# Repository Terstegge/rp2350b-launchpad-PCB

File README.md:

# RP2350 Launchpad

This repository contains the KiCad design files for a TI-style Launchpad
board with the RP2350B microcontroller. The board has the following
features:

- RP2350 microcontroller with 48 GPIOs (8 of these can be used as ADC inputs)
- 8MB of flash and 8MB of PSRAM
- A single red LED (connected to GPIO 38). Can be disabled with a jumper.
- Eight WS2812 RGB LEDs (connected to GPIO 39)
- A reset button
- Two user buttons (S1/S2 connected to GPIO 28/29)
- USB-C socket connected to the target RP2350
- A small button to let the RP2350 start in mass-storage mode for programming.
  This is usually not needed when using the debugger.
- A target isolation jumper block which can be used to completely disconnect
  the targer from power supply and debugging signals.
- A RP2040-based picoprobe debug probe which also forwards UART traffic from
  the target to the connected PC. Three LEDs signal UART RX/TX activity
  and SWD activity.
- Additional header for unused GPIOs of the picoprobe RP2040, which could
  be used for logic analyzer inputs or other purposes.
- Flexible power supply by either using
  * the upper USB-C socket connected to the debugger
  * a connected 3,7V LiPo battery
  * the lower USB-C socket connected to the target

  These three options are selectble with a small switch
- Integrated LiPo charger. The battery will be charged when the board is
  powered from the upper USB-C socket. Charging is signalled with a LED.
  The battery voltage can be read by the RP2350 using ADC channel 7.
- In all power scenarios, 3.3V and 5V are available. When using the
  battery as the power source, the 5V supply is generated with a step-up
  converter.

Why was this board designed? I have been using the MSP432 Launchpad from TI for
quite a while in university classes teaching microcontroller technology.
Unfortunately TI has stopped producing all MSP432-related products. Still we
have lots of TI boosterpack-boards like the Educational Boosterpack MK II.
To be able to use these Boosterpacks also in the future, a new Launchpad had
to be found or designed. The RP2350B is a very interesting microcontroller,
and, what is quite important for educational purposes, it has excellent
documentation. So this board came to life. As far as I know this is the only
RP2350 board including a picoprobe debugger, which makes programming for the
students a lot easier.

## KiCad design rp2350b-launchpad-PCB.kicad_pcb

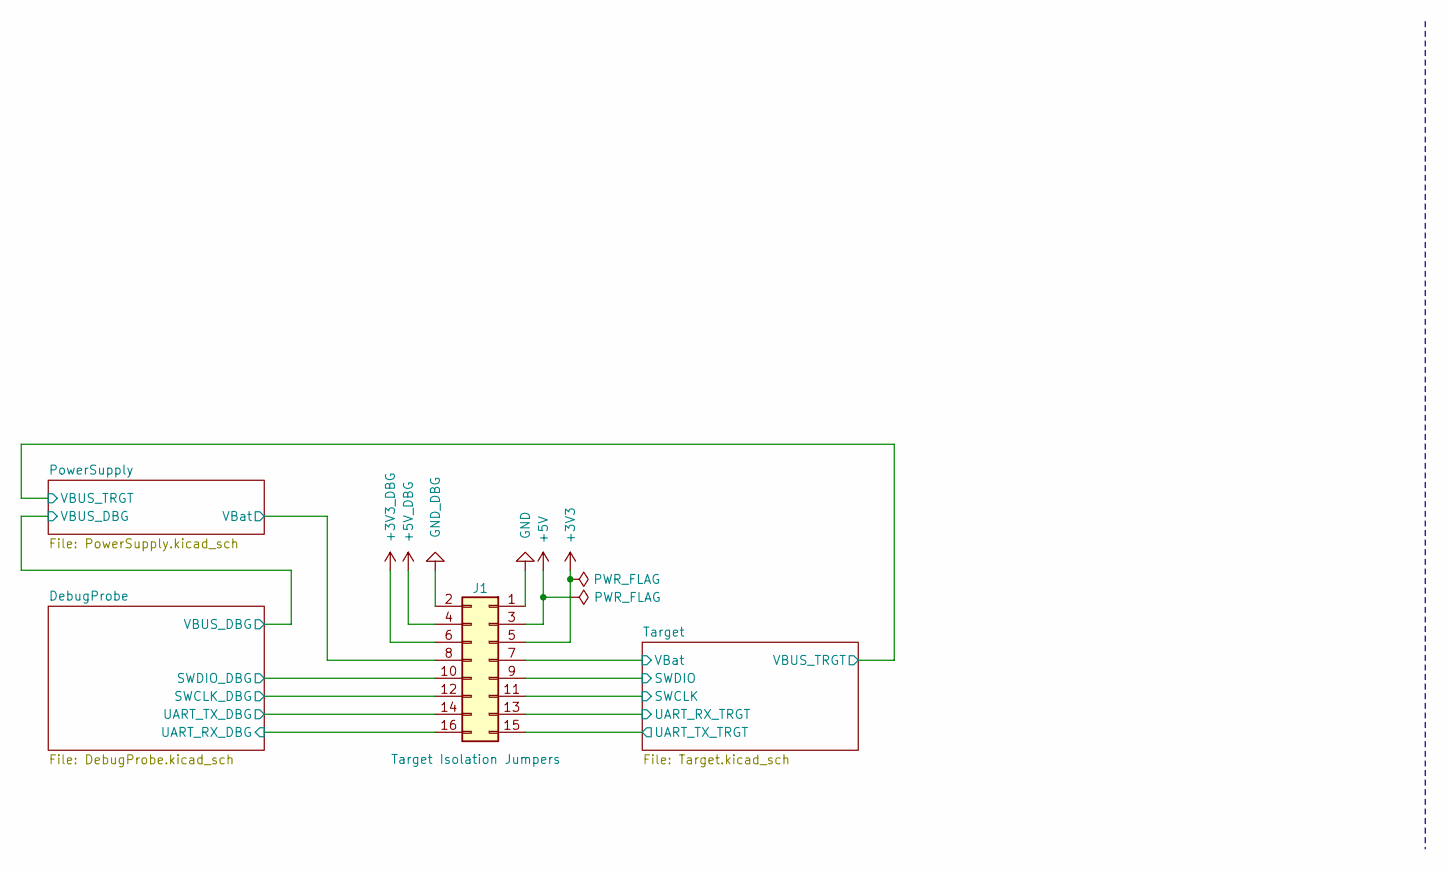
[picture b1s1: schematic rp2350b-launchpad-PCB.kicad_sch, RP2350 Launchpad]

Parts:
J1: Target Isolation Jumpers; PinHeader_2x08_P2.54mm_Vertical

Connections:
+3V3: J1.5; also elsewhere on the board
+3V3_DBG: J1.6; also elsewhere on the board
+5V: J1.3; also elsewhere on the board
+5V_DBG: J1.4; also elsewhere on the board
/DebugProbe/SWCLK_DBG: J1.12; also elsewhere on the board
/DebugProbe/SWDIO_DBG: J1.10; also elsewhere on the board
/DebugProbe/UART_RX_DBG: J1.16; also elsewhere on the board
/DebugProbe/UART_TX_DBG: J1.14; also elsewhere on the board
/PowerSupply/VBat: J1.8; also elsewhere on the board
/Target/ADC7: J1.7; also elsewhere on the board
/Target/SWCLK: J1.11; also elsewhere on the board
/Target/SWDIO: J1.9; also elsewhere on the board
/Target/UART_RX_TRGT: J1.13; also elsewhere on the board
/Target/UART_TX_TRGT: J1.15; also elsewhere on the board
GND: J1.1; also elsewhere on the board
GND_DBG: J1.2; also elsewhere on the board

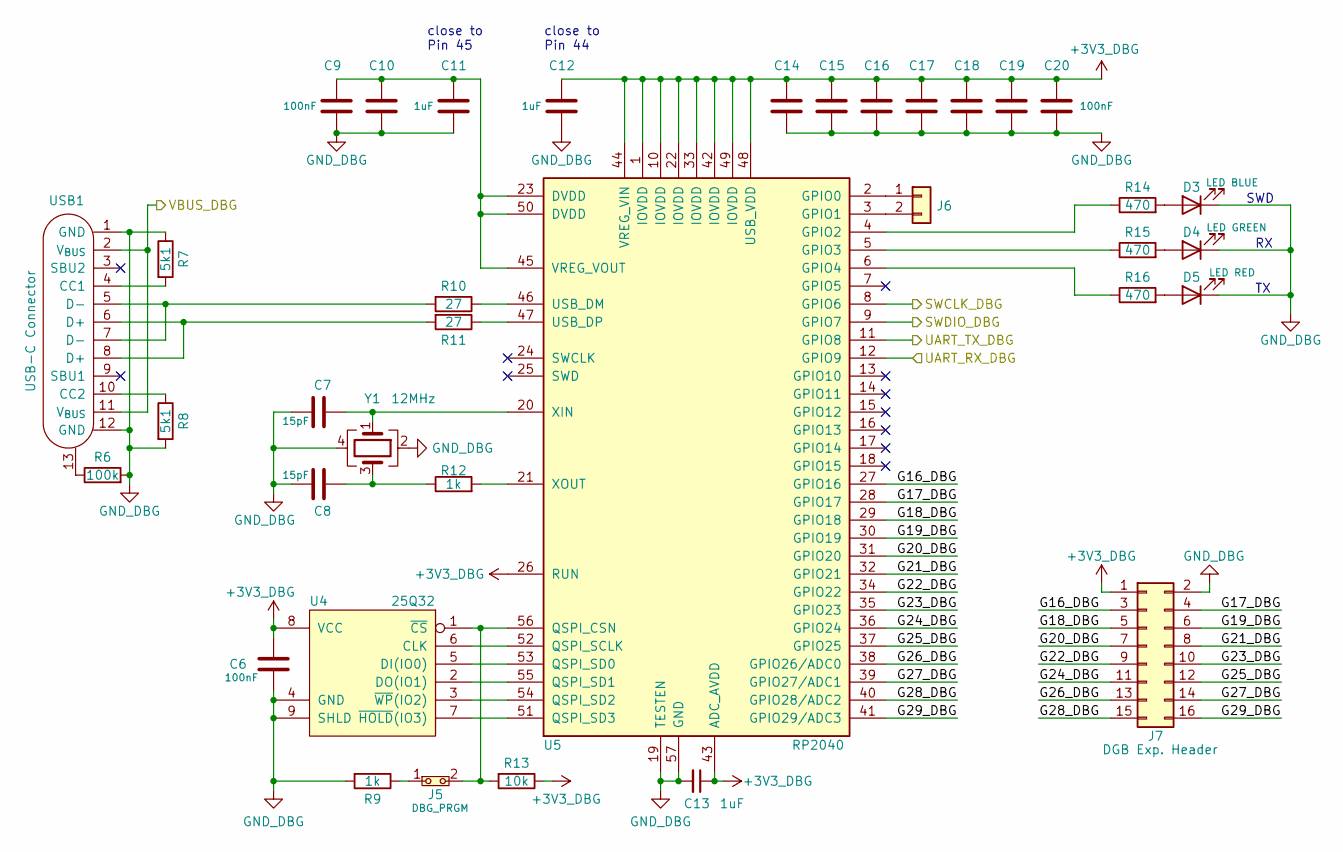
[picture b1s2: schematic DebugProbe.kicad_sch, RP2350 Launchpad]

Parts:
C6, C9, C10, C14, C15, C16, C17, C18, C19, C20: 100nF; C_0603_1608Metric; JLCPCB Part # C14663
C7, C8: 15pF; C_0603_1608Metric; JLCPCB Part # C1644
C11, C12, C13: 1uF; C_0603_1608Metric; JLCPCB Part # C15849
D3: LED BLUE; LED_0603_1608Metric; JLCPCB Part # C2288
D4: LED GREEN; LED_0603_1608Metric; JLCPCB Part # C12624
D5: LED RED; LED_0603_1608Metric; JLCPCB Part # C2286
J5: DBG_PRGM; PinHeader_1x02_P2.54mm_Vertical
J6: UART_DBG; PinHeader_1x02_P2.54mm_Vertical
J7: DGB Exp. Header; PinHeader_2x08_P2.54mm_Vertical
R6: 100k; R_0603_1608Metric; JLCPCB Part # C25803
R7, R8: 5k1; R_0603_1608Metric; JLCPCB Part # C23186
R9, R12: 1k; R_0603_1608Metric; JLCPCB Part # C21190
R10, R11: 27; R_0603_1608Metric; JLCPCB Part # C25190
R13: 10k; R_0603_1608Metric; JLCPCB Part # C25804
R14, R15, R16: 470; R_0603_1608Metric; JLCPCB Part # C23179
U4: 25Q32; WSON-8-1EP_6x5mm_P1.27mm_EP3.4x4.3mm; JLCPCB Part # C571260
U5: RP2040; QFN-56-1EP_7x7mm_P0.4mm_EP3.2x3.2mm; PARTREV 1.6.1; JLCPCB Part # C2040
USB1: USB-C Connector; GT-USB-7010B; JLCPCB Part # C2837092
Y1: 12MHz; Crystal_SMD_Abracon_ABM8AIG-4Pin_3.2x2.5mm; JLCPCB Part # C20625731

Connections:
+3V3_DBG: C6.1, C12.1, C13.1, C14.1, C15.1, C16.1, C17.1, C18.1, C19.1, C20.1, J7.1, R13.1, U4.8 (VCC), U5.1 (IOVDD), U5.10 (IOVDD), U5.22 (IOVDD), U5.26 (RUN), U5.33 (IOVDD), U5.42 (IOVDD), U5.43 (ADC_AVDD), U5.44 (VREG_VIN), U5.48 (USB_VDD), U5.49 (IOVDD); also elsewhere on the board
/DebugProbe/G16_DBG: J7.3, U5.27 (GPIO16)
/DebugProbe/G17_DBG: J7.4, U5.28 (GPIO17)
/DebugProbe/G18_DBG: J7.5, U5.29 (GPIO18)
/DebugProbe/G19_DBG: J7.6, U5.30 (GPIO19)
/DebugProbe/G20_DBG: J7.7, U5.31 (GPIO20)
/DebugProbe/G21_DBG: J7.8, U5.32 (GPIO21)
/DebugProbe/G22_DBG: J7.9, U5.34 (GPIO22)
/DebugProbe/G23_DBG: J7.10, U5.35 (GPIO23)
/DebugProbe/G24_DBG: J7.11, U5.36 (GPIO24)
/DebugProbe/G25_DBG: J7.12, U5.37 (GPIO25)
/DebugProbe/G26_DBG: J7.13, U5.38 (GPIO26/ADC0)
/DebugProbe/G27_DBG: J7.14, U5.39 (GPIO27/ADC1)
/DebugProbe/G28_DBG: J7.15, U5.40 (GPIO28/ADC2)
/DebugProbe/G29_DBG: J7.16, U5.41 (GPIO29/ADC3)
/DebugProbe/SWCLK_DBG: U5.8 (GPIO6); also elsewhere on the board
/DebugProbe/SWDIO_DBG: U5.9 (GPIO7); also elsewhere on the board
/DebugProbe/UART_RX_DBG: U5.12 (GPIO9); also elsewhere on the board
/DebugProbe/UART_TX_DBG: U5.11 (GPIO8); also elsewhere on the board
/DebugProbe/VBUS_DBG: USB1.2 (V_{BUS}), USB1.11 (V_{BUS}); also elsewhere on the board
GND_DBG: C6.2, C7.1, C8.1, C9.2, C10.2, C11.2, C12.2, C13.2, C14.2, C15.2, C16.2, C17.2, C18.2, C19.2, C20.2, D3.1 (K), D4.1 (K), D5.1 (K), J7.2, R6.2, R7.1, R8.2, R9.2, U4.4 (GND), U4.9 (SHLD), U5.19 (TESTEN), U5.57 (GND), USB1.1 (GND), USB1.12 (GND), Y1.2, Y1.4; also elsewhere on the board
unnamed: C8.2, R12.1, Y1.3
unnamed: D3.2 (A), R14.2
unnamed: D4.2 (A), R15.2
unnamed: D5.2 (A), R16.2
unnamed: J5.1, R9.1
unnamed: J6.1, U5.2 (GPIO0)
unnamed: J6.2, U5.3 (GPIO1)
unnamed: R6.1, USB1.13
unnamed: R10.2, USB1.5 (D-), USB1.7 (D-)
unnamed: R11.2, USB1.6 (D+), USB1.8 (D+)
unnamed: U4.6 (CLK), U5.52 (QSPI_SCLK)
unnamed: U4.5 (DI(IO0)), U5.53 (QSPI_SD0)
unnamed: U4.2 (DO(IO1)), U5.55 (QSPI_SD1)
unnamed: J5.2, R13.2, U4.1 (~CS), U5.56 (QSPI_CSN)
unnamed: U4.7 (~HOLD(IO3)), U5.51 (QSPI_SD3)
unnamed: U4.3 (~WP(IO2)), U5.54 (QSPI_SD2)
unnamed: R14.1, U5.4 (GPIO2)
unnamed: R15.1, U5.5 (GPIO3)
unnamed: R16.1, U5.6 (GPIO4)
unnamed: R10.1, U5.46 (USB_DM)
unnamed: R11.1, U5.47 (USB_DP)
unnamed: C9.1, C10.1, C11.1, U5.23 (DVDD), U5.45 (VREG_VOUT), U5.50 (DVDD)
unnamed: C7.2, U5.20 (XIN), Y1.1
unnamed: R12.2, U5.21 (XOUT)
unnamed: R7.2, USB1.4 (CC1)
unnamed: R8.1, USB1.10 (CC2)

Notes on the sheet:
SWD
close to Pin 45
close to Pin 44

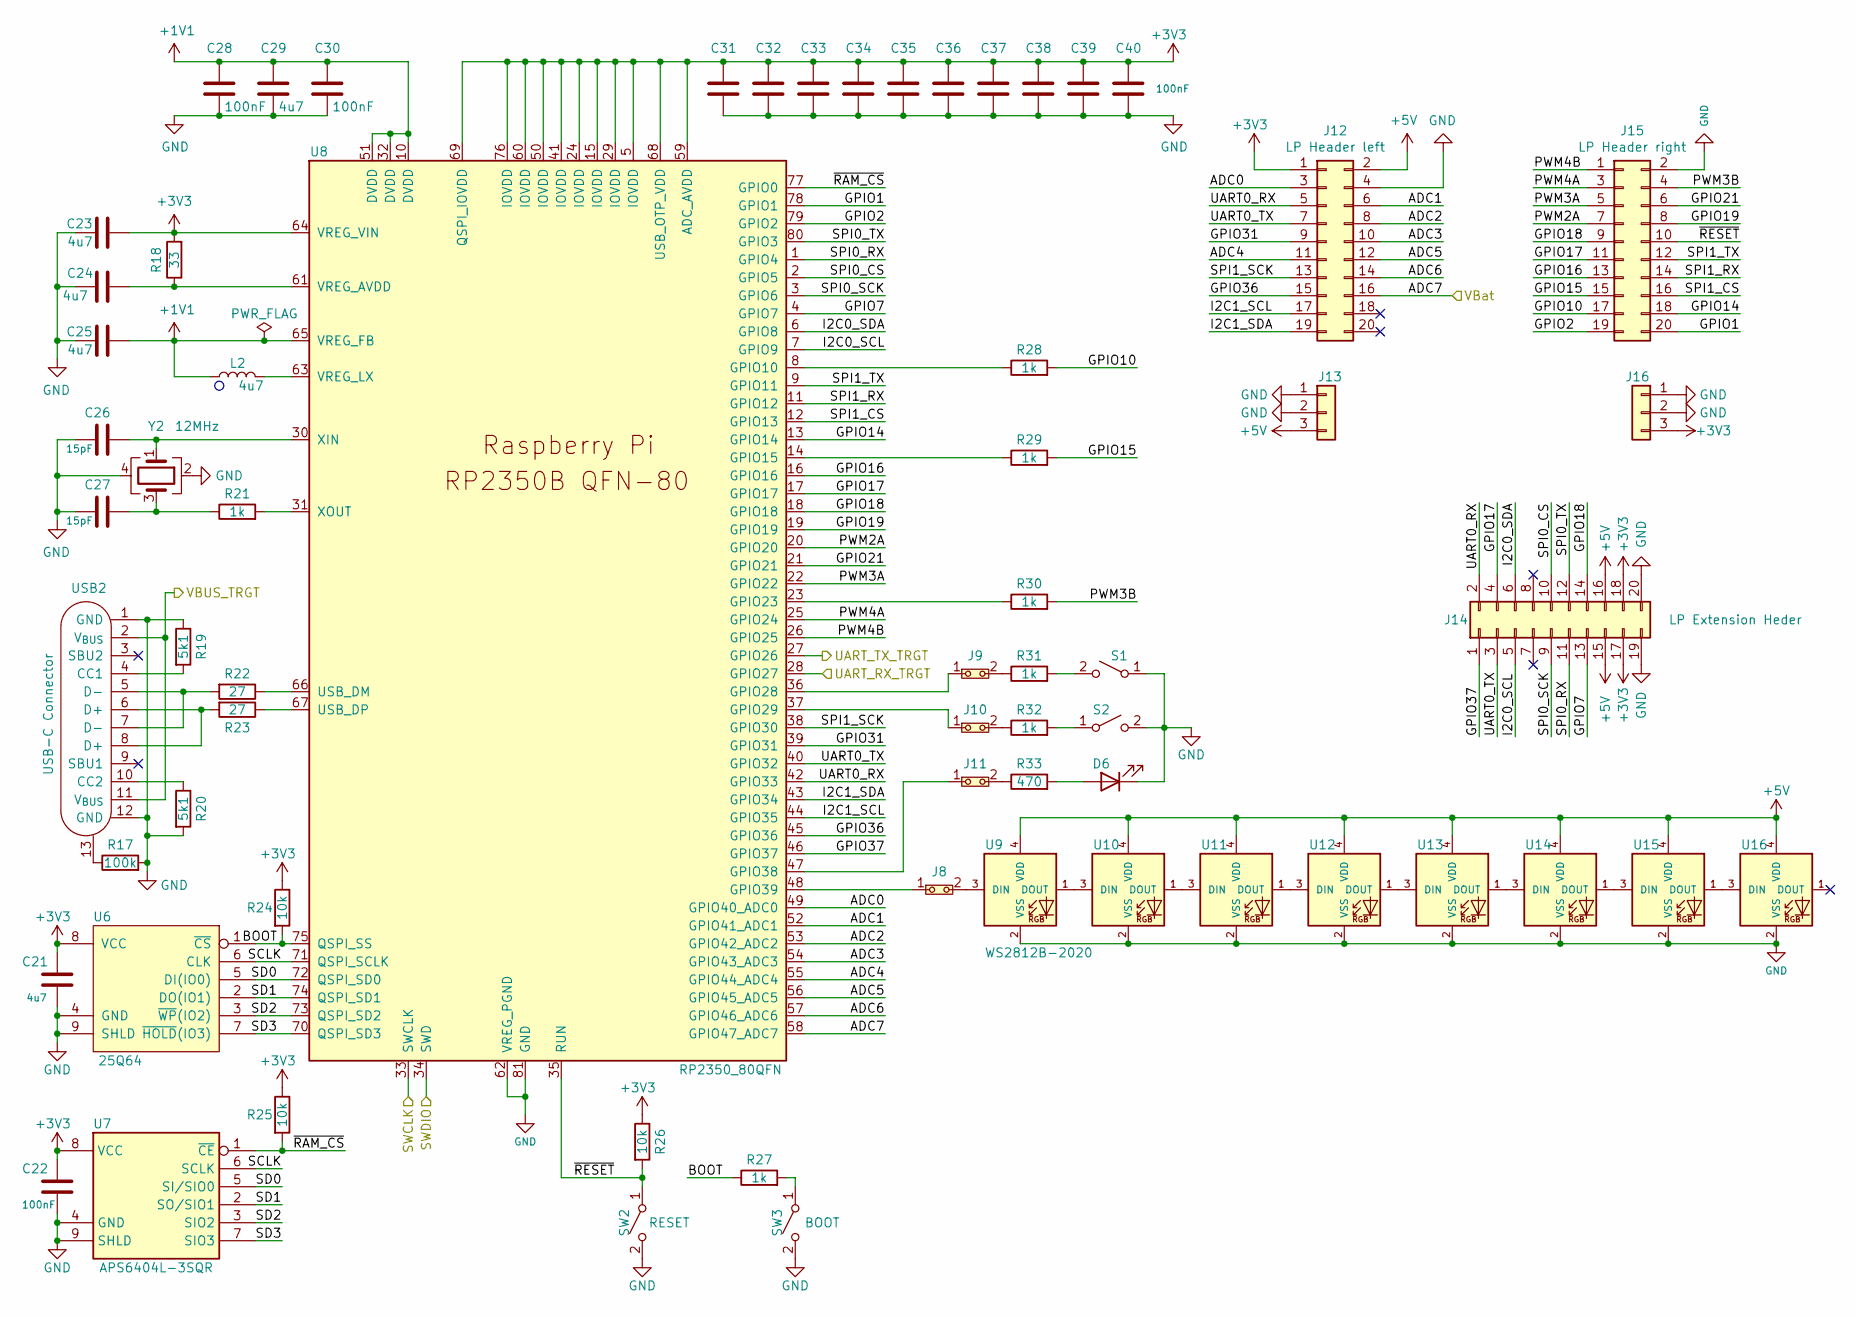
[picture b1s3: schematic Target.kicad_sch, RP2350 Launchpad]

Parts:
C21, C24, C29: 4u7; C_0402_1005Metric; JLCPCB Part # C23733
C22, C28, C30, C31, C32, C33, C34, C35, C36, C37, C38, C39, C40: 100nF; C_0402_1005Metric; JLCPCB Part # C1525
C23, C25: 4u7; C_0603_1608Metric; JLCPCB Part # C19666
C26, C27: 15pF; C_0402_1005Metric; JLCPCB Part # C1548
D6: LED; LED_0603_1608Metric; JLCPCB Part # C2286
J8, J9, J10: Jumper; SolderJumper-2_P1.3mm_Bridged_RoundedPad1.0x1.5mm
J11: Jumper; PinHeader_1x02_P2.54mm_Vertical
J12: LP Header left; PinHeader_2x10_P2.54mm_Vertical
J13, J16: PWR Header; PinHeader_1x03_P2.54mm_Vertical
J14: LP Extension Heder; PinHeader_2x10_P2.54mm_Vertical
J15: LP Header right; PinHeader_2x10_P2.54mm_Vertical
L2: 4u7; AOTA-B201610S3R3-101-T; JLCPCB Part # C42411119
R17: 100k; R_0603_1608Metric; JLCPCB Part # C25803
R18: 33; R_0402_1005Metric; JLCPCB Part # C25161
R19, R20: 5k1; R_0603_1608Metric; JLCPCB Part # C23186
R21, R27, R28, R29, R30, R31, R32: 1k; R_0402_1005Metric; JLCPCB Part # C11702
R22, R23: 27; R_0402_1005Metric; JLCPCB Part # C137890
R24, R25: 10k; R_0402_1005Metric; JLCPCB Part # C25531
R26: 10k; R_0603_1608Metric; JLCPCB Part # C25804
R33: 470; R_0603_1608Metric; JLCPCB Part # C23179
S1: S1; DIPT-1188E; JLCPCB Part # C240289
S2: S2; DIPT-1188E; JLCPCB Part # C240289
SW2: RESET; DIPT-1188E; JLCPCB Part # C240289
SW3: BOOT; KMR2-Switch; JLCPCB Part # C221680
U6: 25Q64; WSON-8-1EP_6x5mm_P1.27mm_EP3.4x4.3mm; JLCPCB Part # C2940197
U7: APS6404L-3SQR; Winbond_USON-8-1EP_3x2mm_P0.5mm_EP0.2x1.6mm; JLCPCB Part # C3040877
U8: RP2350_80QFN; QFN-80-1EP_10x10mm_P0.4mm_EP3.4x3.4mm_ThermalVias; JLCPCB Part # C42415655
U9, U10, U11, U12, U13, U14, U15, U16: WS2812B-2020; JLCPCB Part # C965555
USB2: USB-C Connector; GT-USB-7010B; JLCPCB Part # C2837092
Y2: 12MHz; Crystal_SMD_Abracon_ABM8AIG-4Pin_3.2x2.5mm; JLCPCB Part # C20625731

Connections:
+1V1: C25.2, C28.1, C29.1, C30.1, L2.1, U8.10 (DVDD), U8.32 (DVDD), U8.51 (DVDD), U8.65 (VREG_FB)
+3V3: C21.1, C22.1, C23.2, C31.1, C32.1, C33.1, C34.1, C35.1, C36.1, C37.1, C38.1, C39.1, C40.1, J12.1, J14.17, J14.18, J16.3, R18.2, R24.1, R25.1, R26.1, U6.8 (VCC), U7.8 (VCC), U8.5 (IOVDD), U8.15 (IOVDD), U8.24 (IOVDD), U8.29 (IOVDD), U8.41 (IOVDD), U8.50 (IOVDD), U8.59 (ADC_AVDD), U8.60 (IOVDD), U8.64 (VREG_VIN), U8.68 (USB_OTP_VDD), U8.69 (QSPI_IOVDD), U8.76 (IOVDD); also elsewhere on the board
+5V: J12.2, J13.3, J14.15, J14.16, U9.4 (VDD), U10.4 (VDD), U11.4 (VDD), U12.4 (VDD), U13.4 (VDD), U14.4 (VDD), U15.4 (VDD), U16.4 (VDD); also elsewhere on the board
/PowerSupply/VBUS_TRGT: USB2.2 (V_{BUS}), USB2.11 (V_{BUS}); also elsewhere on the board
/Target/ADC0: J12.3, U8.49 (GPIO40_ADC0)
/Target/ADC1: J12.6, U8.52 (GPIO41_ADC1)
/Target/ADC2: J12.8, U8.53 (GPIO42_ADC2)
/Target/ADC3: J12.10, U8.54 (GPIO43_ADC3)
/Target/ADC4: J12.11, U8.55 (GPIO44_ADC4)
/Target/ADC5: J12.12, U8.56 (GPIO45_ADC5)
/Target/ADC6: J12.14, U8.57 (GPIO46_ADC6)
/Target/ADC7: J12.16, U8.58 (GPIO47_ADC7); also elsewhere on the board
/Target/BOOT: R24.2, R27.1, U6.1 (~CS), U8.75 (QSPI_SS)
/Target/GPIO1: J15.20, U8.78 (GPIO1)
/Target/GPIO2: J15.19, U8.79 (GPIO2)
/Target/GPIO7: J14.13, U8.4 (GPIO7)
/Target/GPIO10: J15.17, R28.2
/Target/GPIO14: J15.18, U8.13 (GPIO14)
/Target/GPIO15: J15.15, R29.2
/Target/GPIO16: J15.13, U8.16 (GPIO16)
/Target/GPIO17: J14.4, J15.11, U8.17 (GPIO17)
/Target/GPIO18: J14.14, J15.9, U8.18 (GPIO18)
/Target/GPIO19: J15.8, U8.19 (GPIO19)
/Target/GPIO21: J15.6, U8.21 (GPIO21)
/Target/GPIO31: J12.9, U8.39 (GPIO31)
/Target/GPIO36: J12.15, U8.45 (GPIO36)
/Target/GPIO37: J14.1, U8.46 (GPIO37)
/Target/I2C0_SCL: J14.5, U8.7 (GPIO9)
/Target/I2C0_SDA: J14.6, U8.6 (GPIO8)
/Target/I2C1_SCL: J12.17, U8.44 (GPIO35)
/Target/I2C1_SDA: J12.19, U8.43 (GPIO34)
/Target/PWM2A: J15.7, U8.20 (GPIO20)
/Target/PWM3A: J15.5, U8.22 (GPIO22)
/Target/PWM3B: J15.4, R30.2
/Target/PWM4A: J15.3, U8.25 (GPIO24)
/Target/PWM4B: J15.1, U8.26 (GPIO25)
/Target/SCLK: U6.6 (CLK), U7.6 (SCLK), U8.71 (QSPI_SCLK)
/Target/SD0: U6.5 (DI(IO0)), U7.5 (SI/SIO0), U8.72 (QSPI_SD0)
/Target/SD1: U6.2 (DO(IO1)), U7.2 (SO/SIO1), U8.74 (QSPI_SD1)
/Target/SD2: U6.3 (~WP(IO2)), U7.3 (SIO2), U8.73 (QSPI_SD2)
/Target/SD3: U6.7 (~HOLD(IO3)), U7.7 (SIO3), U8.70 (QSPI_SD3)
/Target/SPI0_CS: J14.10, U8.2 (GPIO5)
/Target/SPI0_RX: J14.11, U8.1 (GPIO4)
/Target/SPI0_SCK: J14.9, U8.3 (GPIO6)
/Target/SPI0_TX: J14.12, U8.80 (GPIO3)
/Target/SPI1_CS: J15.16, U8.12 (GPIO13)
/Target/SPI1_RX: J15.14, U8.11 (GPIO12)
/Target/SPI1_SCK: J12.13, U8.38 (GPIO30)
/Target/SPI1_TX: J15.12, U8.9 (GPIO11)
/Target/SWCLK: U8.33 (SWCLK); also elsewhere on the board
/Target/SWDIO: U8.34 (SWD); also elsewhere on the board
/Target/UART0_RX: J12.5, J14.2, U8.42 (GPIO33)
/Target/UART0_TX: J12.7, J14.3, U8.40 (GPIO32)
/Target/UART_RX_TRGT: U8.28 (GPIO27); also elsewhere on the board
/Target/UART_TX_TRGT: U8.27 (GPIO26); also elsewhere on the board
/Target/~RAM_CS: R25.2, U7.1 (~CE), U8.77 (GPIO0)
/Target/~RESET: J15.10, R26.2, SW2.1 (A), U8.35 (RUN)
GND: C21.2, C22.2, C23.1, C24.2, C25.1, C26.1, C27.1, C28.2, C29.2, C30.2, C31.2, C32.2, C33.2, C34.2, C35.2, C36.2, C37.2, C38.2, C39.2, C40.2, D6.1 (K), J12.4, J13.1, J13.2, J14.19, J14.20, J15.2, J16.1, J16.2, R17.2, R19.1, R20.2, S1.1 (A), S2.2 (B), SW2.2 (B), SW3.2 (B), U6.4 (GND), U6.9 (SHLD), U7.4 (GND), U7.9 (SHLD), U8.62 (VREG_PGND), U8.81 (GND), U9.2 (VSS), U10.2 (VSS), U11.2 (VSS), U12.2 (VSS), U13.2 (VSS), U14.2 (VSS), U15.2 (VSS), U16.2 (VSS), USB2.1 (GND), USB2.12 (GND), Y2.2, Y2.4; also elsewhere on the board
unnamed: C27.2, R21.1, Y2.3
unnamed: D6.2 (A), R33.2
unnamed: J9.2, R31.1
unnamed: J10.2, R32.1
unnamed: J11.2, R33.1
unnamed: R17.1, USB2.13
unnamed: R22.2, USB2.5 (D-), USB2.7 (D-)
unnamed: R23.2, USB2.6 (D+), USB2.8 (D+)
unnamed: R31.2, S1.2 (B)
unnamed: R32.2, S2.1 (A)
unnamed: R27.2, SW3.1 (A)
unnamed: R28.1, U8.8 (GPIO10)
unnamed: R29.1, U8.14 (GPIO15)
unnamed: R30.1, U8.23 (GPIO23)
unnamed: J9.1, U8.36 (GPIO28)
unnamed: J10.1, U8.37 (GPIO29)
unnamed: J11.1, U8.47 (GPIO38)
unnamed: J8.1, U8.48 (GPIO39)
unnamed: R22.1, U8.66 (USB_DM)
unnamed: R23.1, U8.67 (USB_DP)
unnamed: C24.1, R18.1, U8.61 (VREG_AVDD)
unnamed: L2.2, U8.63 (VREG_LX)
unnamed: C26.2, U8.30 (XIN), Y2.1
unnamed: R21.2, U8.31 (XOUT)
unnamed: J8.2, U9.3 (DIN)
unnamed: U9.1 (DOUT), U10.3 (DIN)
unnamed: U10.1 (DOUT), U11.3 (DIN)
unnamed: U11.1 (DOUT), U12.3 (DIN)
unnamed: U12.1 (DOUT), U13.3 (DIN)
unnamed: U13.1 (DOUT), U14.3 (DIN)
unnamed: U14.1 (DOUT), U15.3 (DIN)
unnamed: U15.1 (DOUT), U16.3 (DIN)
unnamed: R19.2, USB2.4 (CC1)
unnamed: R20.1, USB2.10 (CC2)

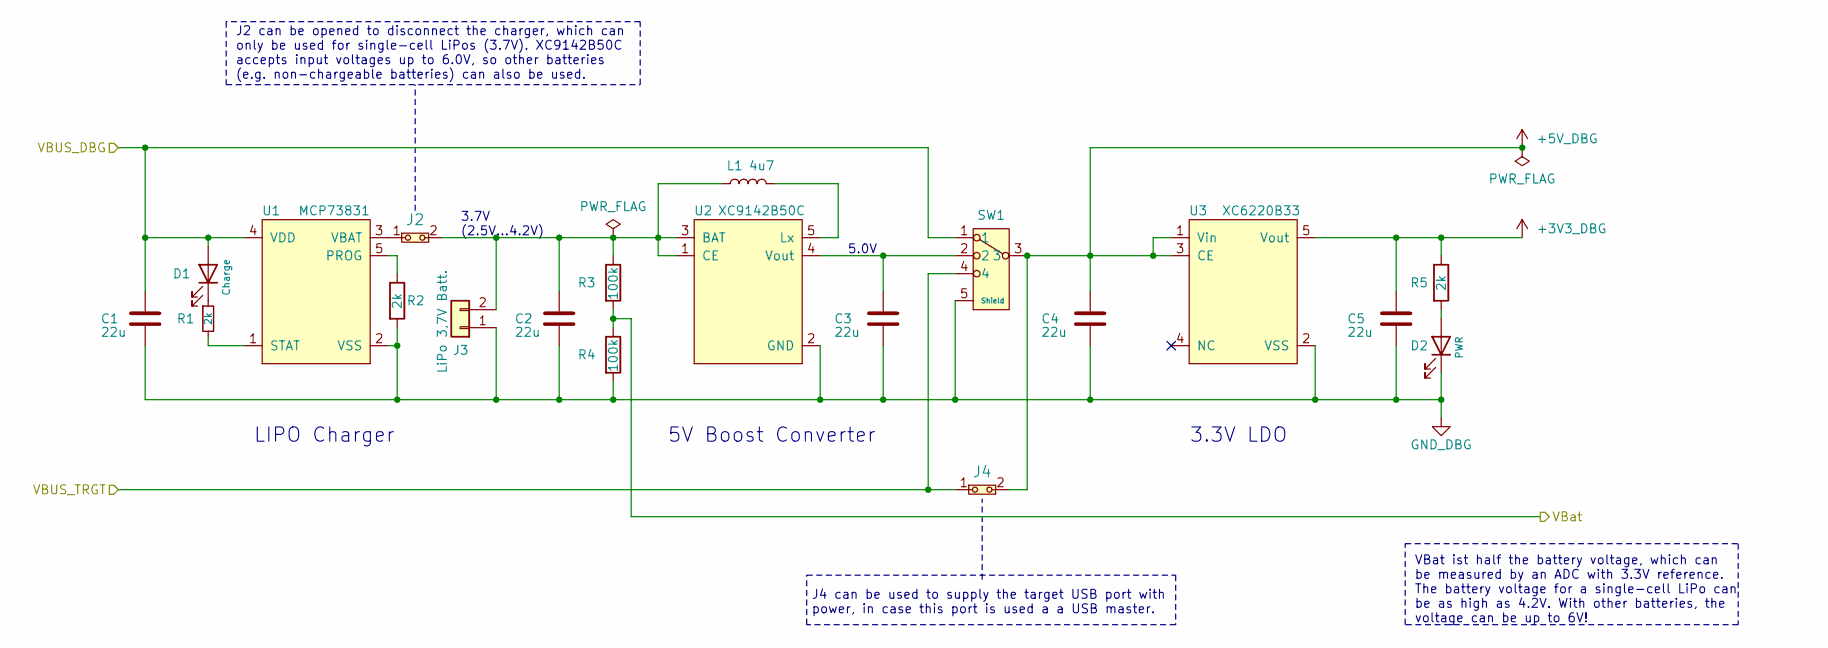
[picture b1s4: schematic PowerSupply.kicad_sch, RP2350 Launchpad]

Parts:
C1, C2, C3, C4, C5: 22u; C_0805_2012Metric; JLCPCB Part # C45783
D1: Charge; LED_0603_1608Metric; JLCPCB Part # C84269
D2: PWR; LED_0603_1608Metric; JLCPCB Part # C84269
J2: Jumper; SolderJumper-2_P1.3mm_Open_RoundedPad1.0x1.5mm
J3: LiPo 3,7V Batt.; JST-S2B-PH-KL
J4: Jumper; PinHeader_1x02_P2.54mm_Vertical
L1: 4u7; AOTA-B201610S3R3-101-T; JLCPCB Part # C42411119
R1, R2, R5: 2k; R_0603_1608Metric; JLCPCB Part # C22975
R3, R4: 100k; R_0603_1608Metric; JLCPCB Part # C25803
SW1: Power Select; PCM13SMTR; JLCPCB Part # C221842
U1: MCP73831; SOT-23-5; JLCPCB Part # C424093
U2: XC9142B50C; SOT-23-5; JLCPCB Part # C2468807
U3: XC6220B33; SOT-23-5; JLCPCB Part # C22466451

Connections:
+3V3_DBG: C5.2, R5.1, U3.5 (Vout); also elsewhere on the board
+5V_DBG: C4.2, J4.2, SW1.3, U3.1 (Vin), U3.3 (CE); also elsewhere on the board
/DebugProbe/VBUS_DBG: C1.2, D1.2 (A), SW1.1, U1.4 (VDD); also elsewhere on the board
/PowerSupply/VBUS_TRGT: J4.1, SW1.4; also elsewhere on the board
/PowerSupply/VBat: R3.2, R4.1; also elsewhere on the board
GND_DBG: C1.1, C2.1, C3.1, C4.1, C5.1, D2.1 (K), J3.1, R2.2, R4.2, SW1.5 (Shield), U1.2 (VSS), U2.2 (GND), U3.2 (VSS); also elsewhere on the board
unnamed: D1.1 (K), R1.1
unnamed: D2.2 (A), R5.2
unnamed: C2.2, J2.2, J3.2, L1.1, R3.1, U2.1 (CE), U2.3 (BAT)
unnamed: R2.1, U1.5 (PROG)
unnamed: R1.2, U1.1 (STAT)
unnamed: J2.1, U1.3 (VBAT)
unnamed: L1.2, U2.5 (Lx)
unnamed: C3.2, SW1.2, U2.4 (Vout)

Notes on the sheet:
3.7V (2.5V...4.2V)
3.3V LDO
5V Boost Converter
VBat ist half the battery voltage, which can be measured by an ADC with 3.3V reference. The battery voltage for a single-cell LiPo can be as high as 4.2V. With other batteries, the voltage can be up to 6V!
J4 can be used to supply the target USB port with power, in case this port is used a a USB master.
LIPO Charger
J2 can be opened to disconnect the charger, which can only be used for single-cell LiPos (3.7V). XC9142B50C accepts input voltages up to 6.0V, so other batteries (e.g. non-chargeable batteries) can also be used.
5.0V

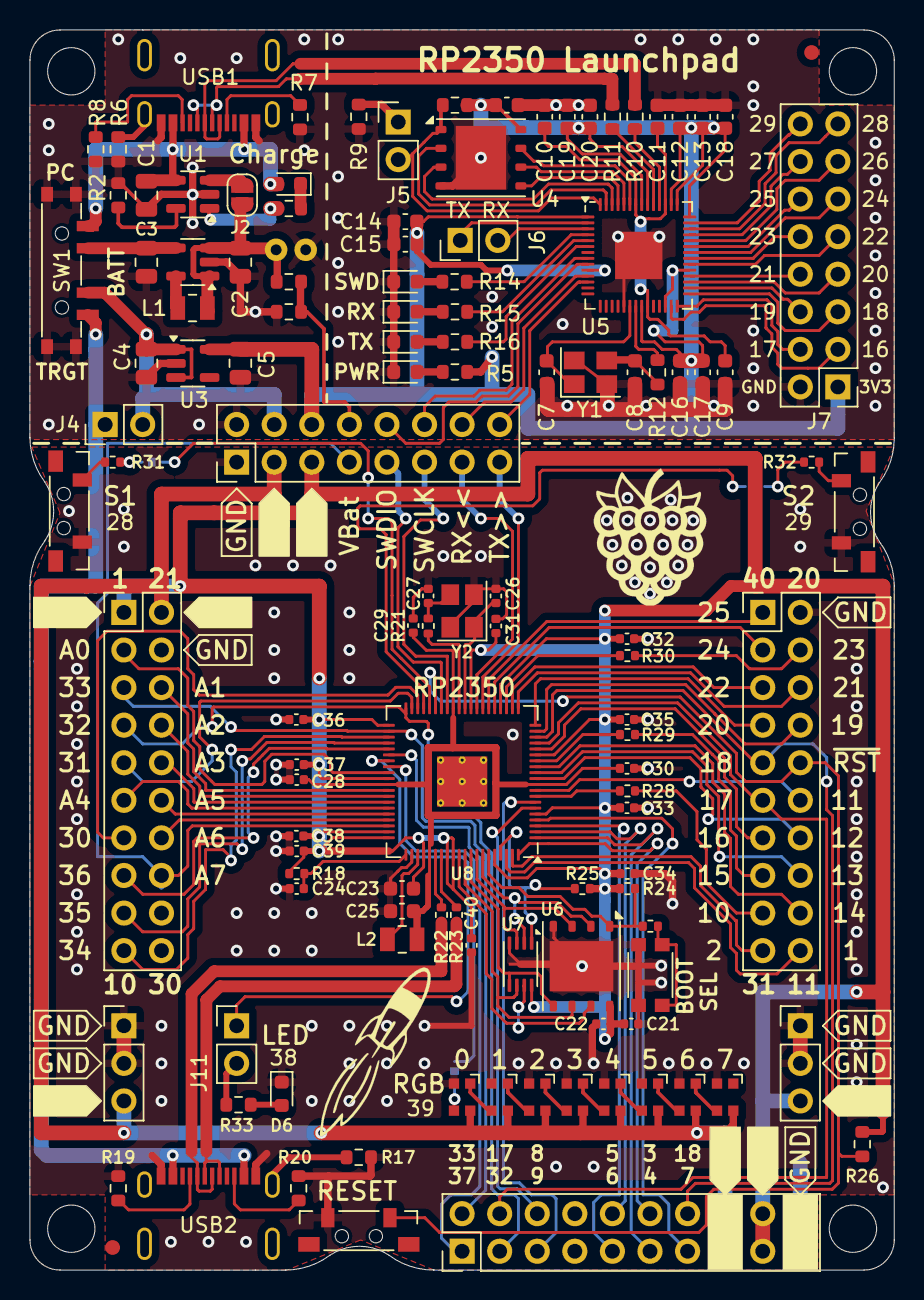
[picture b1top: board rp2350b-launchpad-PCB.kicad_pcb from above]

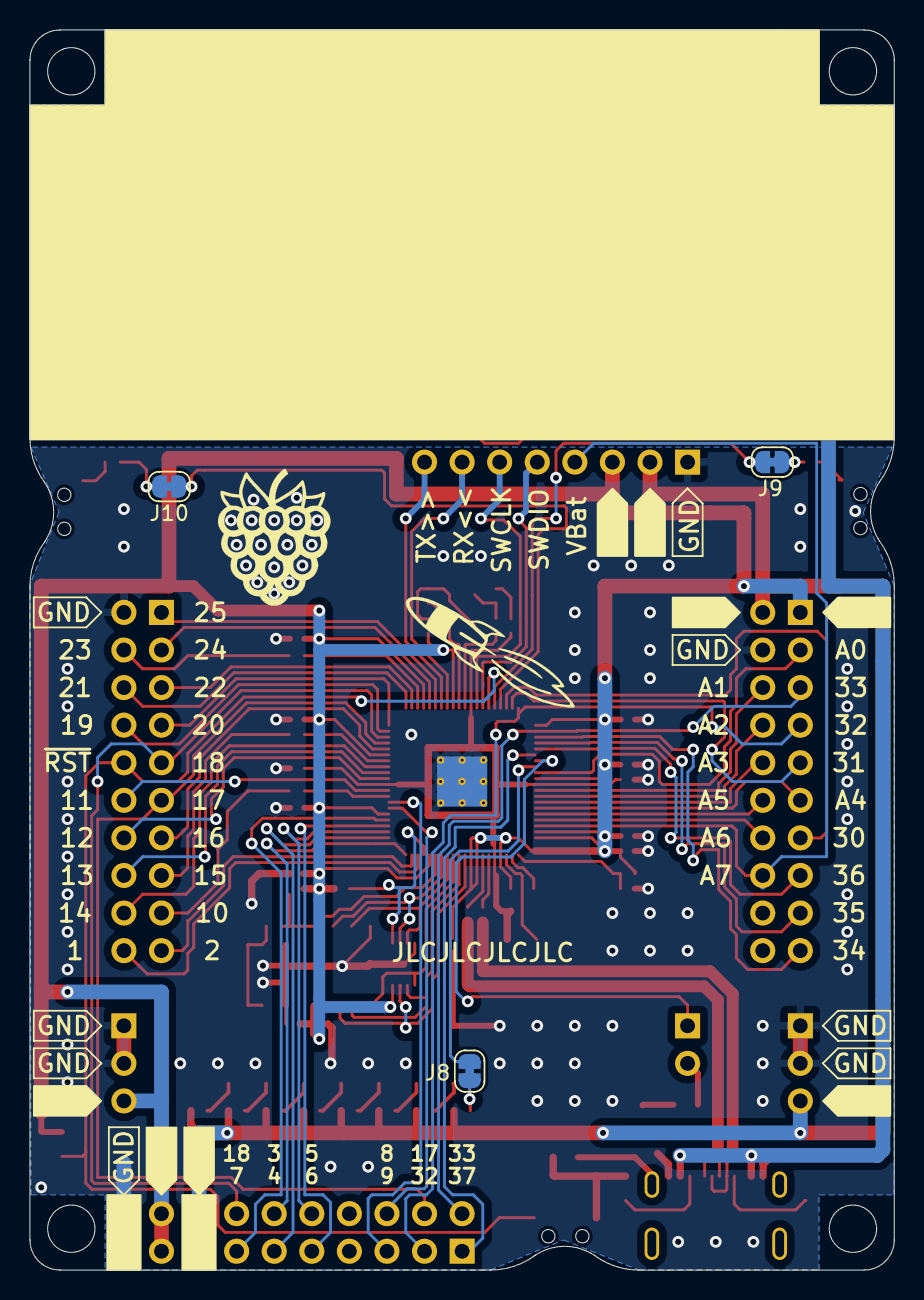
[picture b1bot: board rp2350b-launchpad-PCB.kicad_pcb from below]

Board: 2 copper layers, 58.4 x 83.8 mm, 122 parts (4 on the bottom side), 149 nets.

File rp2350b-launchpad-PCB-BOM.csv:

"ID";"Bezeichner";"Footprint";"Stückzahl";"Bezeichnung";"Anbieter und Referenz";
1;"C22,C33,C36,C38,C40,C37,C32,C31,C35,C34,C39";"C_0402_1005Metric";11;"100nF";;;
2;"C1,C2,C4,C5,C3";"C_0805_2012Metric";5;"22u";;;
3;"C7,C8";"C_0603_1608Metric";2;"15pF";;;
4;"C9,C10,C14,C16,C18,C20,C19,C17,C15,C6";"C_0603_1608Metric";10;"100nF";;;
5;"C12,C13,C11";"C_0603_1608Metric";3;"1uF";;;
6;"D1";"LED_0603_1608Metric";1;"Charge";;;
7;"D2";"LED_0603_1608Metric";1;"PWR";;;
8;"D3";"LED_0603_1608Metric";1;"BLUE";;;
9;"D4";"LED_0603_1608Metric";1;"GREEN";;;
10;"D5";"LED_0603_1608Metric";1;"RED";;;
11;"J12";"PinHeader_2x10_P2.54mm_Vertical";1;"LP Header left";;;
12;"J13,J16";"PinHeader_1x03_P2.54mm_Vertical";2;"PWR Header";;;
13;"J14";"PinHeader_2x10_P2.54mm_Vertical";1;"LP Extension Heder";;;
14;"J15";"PinHeader_2x10_P2.54mm_Vertical";1;"LP Header right";;;
15;"J2,J10,J9,J8";"SolderJumper-2_P1.3mm_Bridged_RoundedPad1.0x1.5mm";4;"Jumper";;;
16;"J5";"PinHeader_1x02_P2.54mm_Vertical";1;"DBG_PRGM";;;
17;"J7";"PinHeader_2x08_P2.54mm_Vertical";1;"DGB Exp. Header";;;
18;"L1";"L_1008_2520Metric";1;"4u7";;;
19;"R27,R30,R32,R21,R29,R28,R31";"R_0402_1005Metric";7;"1k";;;
20;"R24,R25";"R_0402_1005Metric";2;"10k";;;
21;"R1,R5,R9,R12";"R_0603_1608Metric";4;"1k";;;
22;"R3,R4,R6,R17";"R_0603_1608Metric";4;"100k";;;
23;"R10,R11";"R_0603_1608Metric";2;"27";;;
24;"R13,R26";"R_0603_1608Metric";2;"10k";;;
25;"R15,R16,R14,R33";"R_0603_1608Metric";4;"470";;;
26;"SW2";"DIPT-1188E";1;"RESET";;;
27;"U2";"SOT-23-5";1;"XC9142B50C";;;
28;"Y1,Y2";"Crystal_SMD_TXC_7M-4Pin_3.2x2.5mm";2;"12MHz";;;
29;"U4";"WSON-8-1EP_6x5mm_P1.27mm_EP3.4x4.3mm";1;"25Q32";;;
30;"J6";"PinHeader_1x02_P2.54mm_Vertical";1;"UART_DBG";;;
31;"U5";"QFN-56-1EP_7x7mm_P0.4mm_EP3.2x3.2mm";1;"RP2040";;;
32;"J1";"PinHeader_2x08_P2.54mm_Vertical";1;"Target Isolation Jumpers";;;
33;"U3";"SOT-23-5";1;"XC6220B33";;;
34;"U1";"SOT-23-5";1;"MCP73831";;;
35;"R2";"R_0603_1608Metric";1;"2k";;;
36;"REF**,REF**";"Fiducial_1mm_Mask2mm";2;"Fiducial_1mm_Mask2mm";;;
37;"U10,U11,U12,U13,U14,U15,U16,U9";"WS2812B-2020";8;"WS2812B-2020";;;
38;"SW3";"KMR2-Switch";1;"BOOT";;;
39;"G***,G***";"raspberry";2;"LOGO";;;
40;"SW1";"PCM13SMTR";1;"Switch_SP3T";;;
41;"C23,C25";"C_0603_1608Metric";2;"4.7u";;;
42;"C21";"C_0402_1005Metric";1;"4,7u";;;
43;"R19,R8,R20,R7";"R_0603_1608Metric";4;"5k1";;;
44;"U7";"Winbond_USON-8-1EP_3x2mm_P0.5mm_EP0.2x1.6mm";1;"APS6404L-3SQR";;;
45;"R22,R23";"R_0402_1005Metric";2;"27";;;
46;"L2";"AOTA-B201610S3R3-101-T";1;"3u3";;;
47;"C29,C24";"C_0402_1005Metric";2;"4.7u";;;
48;"C30,C28";"C_0402_1005Metric";2;"100n";;;
49;"C27,C26";"C_0402_1005Metric";2;"15pF";;;
50;"USB2,USB1";"GT-USB-7010B";2;"USB-C-Socket";;;
51;"J11,J4";"PinHeader_1x02_P2.54mm_Vertical";2;"Jumper";;;
52;"S1";"DIPT-1188E";1;"S1";;;
53;"R18";"R_0402_1005Metric";1;"33";;;
54;"S2";"DIPT-1188E";1;"S2";;;
55;"D6";"LED_0603_1608Metric";1;"LED";;;
56;"U6";"WSON-8-1EP_6x5mm_P1.27mm_EP3.4x4.3mm";1;"25Q64";;;
57;"U8";"QFN-80-1EP_10x10mm_P0.4mm_EP3.4x3.4mm_ThermalVias";1;"RP2350_80QFN";;;
58;"J3";"JST-S2B-PH-KL";1;"LiPo 3,7V Batt.";;;

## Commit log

2024-09-01 Added first file :)
2024-11-22 First version of RP2350B Launchpad finished!
2024-11-22 small change to PCB (GND area under MCU).
2024-11-22 Renamed files.
2024-11-22 Added .gitignore file
2024-11-22 Fixes to manual renaming...
2024-11-22 More fixes...
2024-11-22 Changed target flash to 16 MiB type.
2024-11-22 Footprint cleanup.
2024-11-22 Fixed gerber file names.
2024-11-23 Renumbering parts on target.
2025-01-09 Ready for Version v1.0. Changed PCB to comply with RPi design 'rules'. Without using special components and PCB designs, the PCB may not be produced :\
2025-02-11 Updated BOM and pos files for v1.0
2025-02-13 Updates for better JLCPCB processing. Version is now 1.1
2025-02-22 Ready for v1.1
2025-03-27 Last small fixes for v1.11
2025-04-07 Work on README
2025-04-07 Added images.
2025-04-07 Small typo
2025-04-07 A last typo...
2025-04-07 Changed README title...
2025-04-07 Added battery volatage reading in README.

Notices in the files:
DebugProbe.kicad_sch:
(C) 2024 A. Terstegge
rp2350b-launchpad-PCB.kicad_pcb:
© 2025 A. Terstegge
